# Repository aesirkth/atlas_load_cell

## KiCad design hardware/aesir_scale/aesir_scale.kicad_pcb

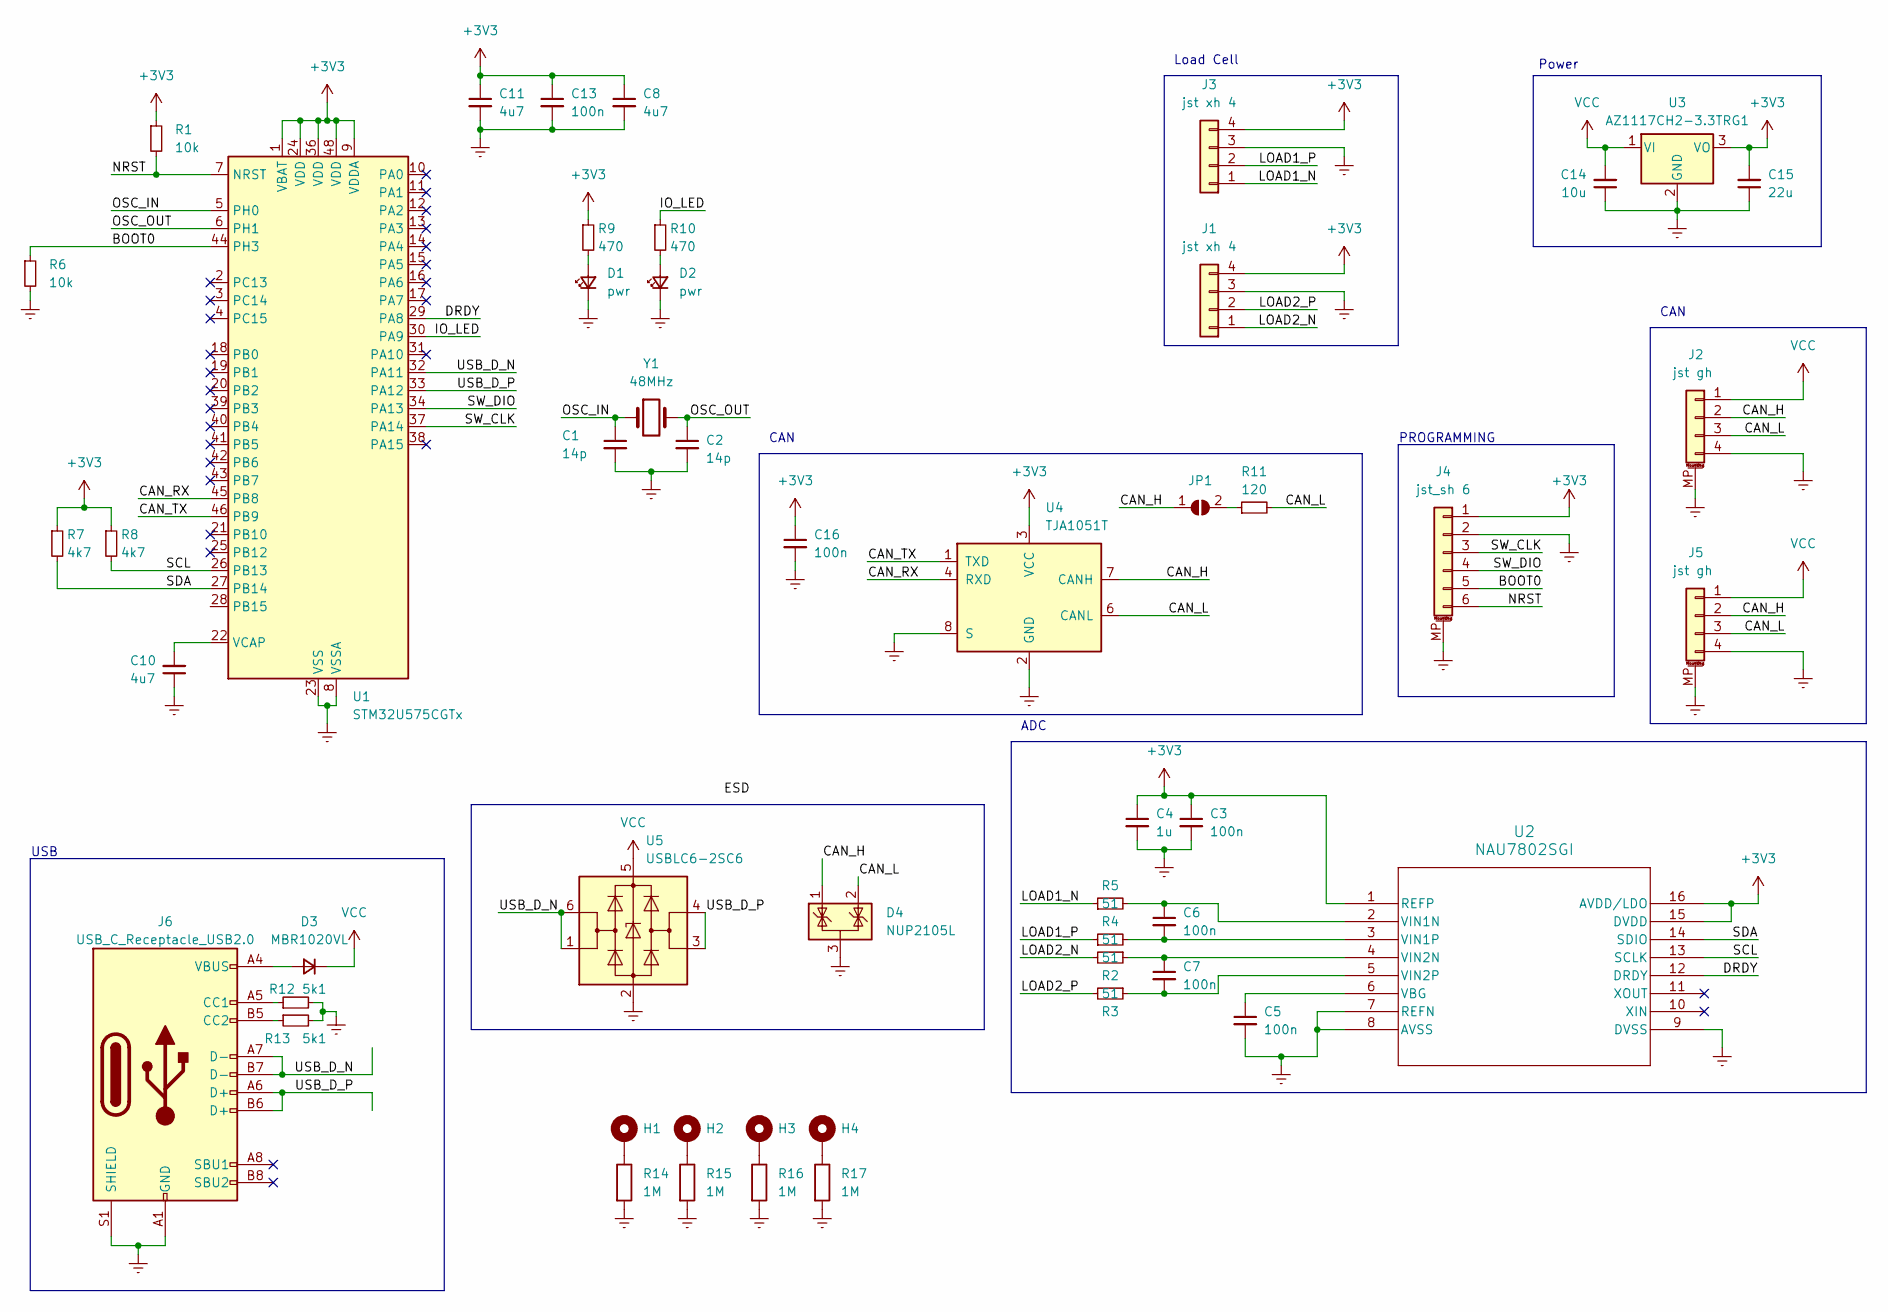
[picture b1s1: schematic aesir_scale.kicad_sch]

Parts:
C1, C2: 14p; C_0603_1608Metric_Pad1.08x0.95mm_HandSolder
C3, C5, C6, C7, C13, C16: 100n; C_0603_1608Metric_Pad1.08x0.95mm_HandSolder
C4: 1u; C_0603_1608Metric_Pad1.08x0.95mm_HandSolder
C8, C10, C11: 4u7; C_0603_1608Metric_Pad1.08x0.95mm_HandSolder
C14: 10u; C_0603_1608Metric_Pad1.08x0.95mm_HandSolder
C15: 22u; C_0603_1608Metric_Pad1.08x0.95mm_HandSolder
D1, D2: pwr; LED_0805_2012Metric_Pad1.15x1.40mm_HandSolder
D3: MBR1020VL; D_SOD-323_HandSoldering
D4: NUP2105L; SOT-23
H1, H2, H3, H4: MountingHole; MountingHole_3.2mm_M3_ISO7380_Pad
J1, J3: jst xh 4; JST_XH_B4B-XH-A_1x04_P2.50mm_Vertical
J2, J5: jst gh; JST_GH_SM04B-GHS-TB_1x04-1MP_P1.25mm_Horizontal
J4: jst_sh 6; JST_SH_SM06B-SRSS-TB_1x06-1MP_P1.00mm_Horizontal
J6: USB_C_Receptacle_USB2.0; USB_C_Receptacle_Palconn_UTC16-G
JP1: SolderJumper_2_Open; SolderJumper-2_P1.3mm_Open_TrianglePad1.0x1.5mm
R1, R6: 10k; R_0603_1608Metric_Pad0.98x0.95mm_HandSolder
R2, R3, R4, R5: 51; R_0603_1608Metric_Pad0.98x0.95mm_HandSolder
R7, R8: 4k7; R_0603_1608Metric_Pad0.98x0.95mm_HandSolder
R9, R10: 470; R_0603_1608Metric_Pad0.98x0.95mm_HandSolder
R11: 120; R_0603_1608Metric_Pad0.98x0.95mm_HandSolder
R12, R13: 5k1; R_0603_1608Metric
R14, R15, R16, R17: 1M; R_0603_1608Metric_Pad0.98x0.95mm_HandSolder
U1: STM32U575CGTx; LQFP-48_7x7mm_P0.5mm
U2: NAU7802SGI; SOI16_NAU7802SGI_NUV
U3: AZ1117CH2-3.3TRG1; SOT-223-3_TabPin2
U4: TJA1051T; SOIC-8_3.9x4.9mm_P1.27mm
U5: USBLC6-2SC6; SOT-23-6
Y1: 48MHz; Crystal_SMD_0603-2Pin_6.0x3.5mm_HandSoldering

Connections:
+3V3: C3.1, C4.1, C8.1, C11.1, C13.1, C15.2, C16.1, J1.4, J3.4, J4.1, R1.1, R7.1, R8.1, R9.1, U1.1 (VBAT), U1.9 (VDDA), U1.24 (VDD), U1.36 (VDD), U1.48 (VDD), U2.1 (REFP), U2.15 (DVDD), U2.16 (AVDD/LDO), U3.3 (VO), U4.3 (VCC)
/BOOT0: J4.5, R6.1, U1.44 (PH3)
/CAN_H: D4.1 (K), J2.2, J5.2, JP1.1 (A), U4.7 (CANH)
/CAN_L: D4.2 (K), J2.3, J5.3, R11.2, U4.6 (CANL)
/CAN_RX: U1.45 (PB8), U4.4 (RXD)
/CAN_TX: U1.46 (PB9), U4.1 (TXD)
/DRDY: U1.29 (PA8), U2.12 (DRDY)
/IO_LED: R10.1, U1.30 (PA9)
/LOAD1_N: J3.1, R5.1
/LOAD1_P: J3.2, R4.1
/LOAD2_N: J1.1, R2.2
/LOAD2_P: J1.2, R3.2
/NRST: J4.6, R1.2, U1.7 (NRST)
/OSC_IN: C1.1, U1.5 (PH0), Y1.1
/OSC_OUT: C2.1, U1.6 (PH1), Y1.2
/SCL: R8.2, U1.26 (PB13), U2.13 (SCLK)
/SDA: R7.2, U1.27 (PB14), U2.14 (SDIO)
/SW_CLK: J4.3, U1.37 (PA14)
/SW_DIO: J4.4, U1.34 (PA13)
/USB_D_N: J6.A7 (D-), J6.B7 (D-), U1.32 (PA11), U5.1 (I/O1), U5.6 (I/O1)
/USB_D_P: J6.A6 (D+), J6.B6 (D+), U1.33 (PA12), U5.3 (I/O2), U5.4 (I/O2)
Earth: C1.2, C2.2, C3.2, C4.2, C5.2, C8.2, C10.1, C11.2, C13.2, C14.1, C15.1, C16.2, D1.1 (K), D2.1 (K), D4.3 (A), J1.3, J2.4, J2.MP (MountPin), J3.3, J4.2, J4.MP (MountPin), J5.4, J5.MP (MountPin), J6.A1 (GND), J6.A12 (GND), J6.B1 (GND), J6.B12 (GND), J6.S1 (SHIELD), R6.2, R12.2, R13.2, R14.2, R15.2, R16.2, R17.2, U1.8 (VSSA), U1.23 (VSS), U1.35 (VSS), U1.47 (VSS), U2.7 (REFN), U2.8 (AVSS), U2.9 (DVSS), U3.2 (GND), U4.2 (GND), U4.8 (S), U5.2 (GND)
unnamed: D1.2 (A), R9.2
unnamed: D2.2 (A), R10.2
unnamed: D3.2 (A), J6.A4 (VBUS), J6.A9 (VBUS), J6.B4 (VBUS), J6.B9 (VBUS)
unnamed: H1.1, R14.1
unnamed: H2.1, R15.1
unnamed: H3.1, R16.1
unnamed: H4.1, R17.1
unnamed: J6.A5 (CC1), R12.1
unnamed: J6.B5 (CC2), R13.1
unnamed: JP1.2 (B), R11.1
unnamed: C10.2, U1.22 (VCAP)
unnamed: C5.1, U2.6 (VBG)
unnamed: C6.1, R5.2, U2.2 (VIN1N)
unnamed: C6.2, R4.2, U2.3 (VIN1P)
unnamed: C7.1, R2.1, U2.4 (VIN2N)
unnamed: C7.2, R3.1, U2.5 (VIN2P)
VCC: C14.2, D3.1 (K), J2.1, J5.1, U3.1 (VI), U5.5 (VBUS)

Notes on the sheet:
Power
CAN
USB
PROGRAMMING
ADC
Load Cell

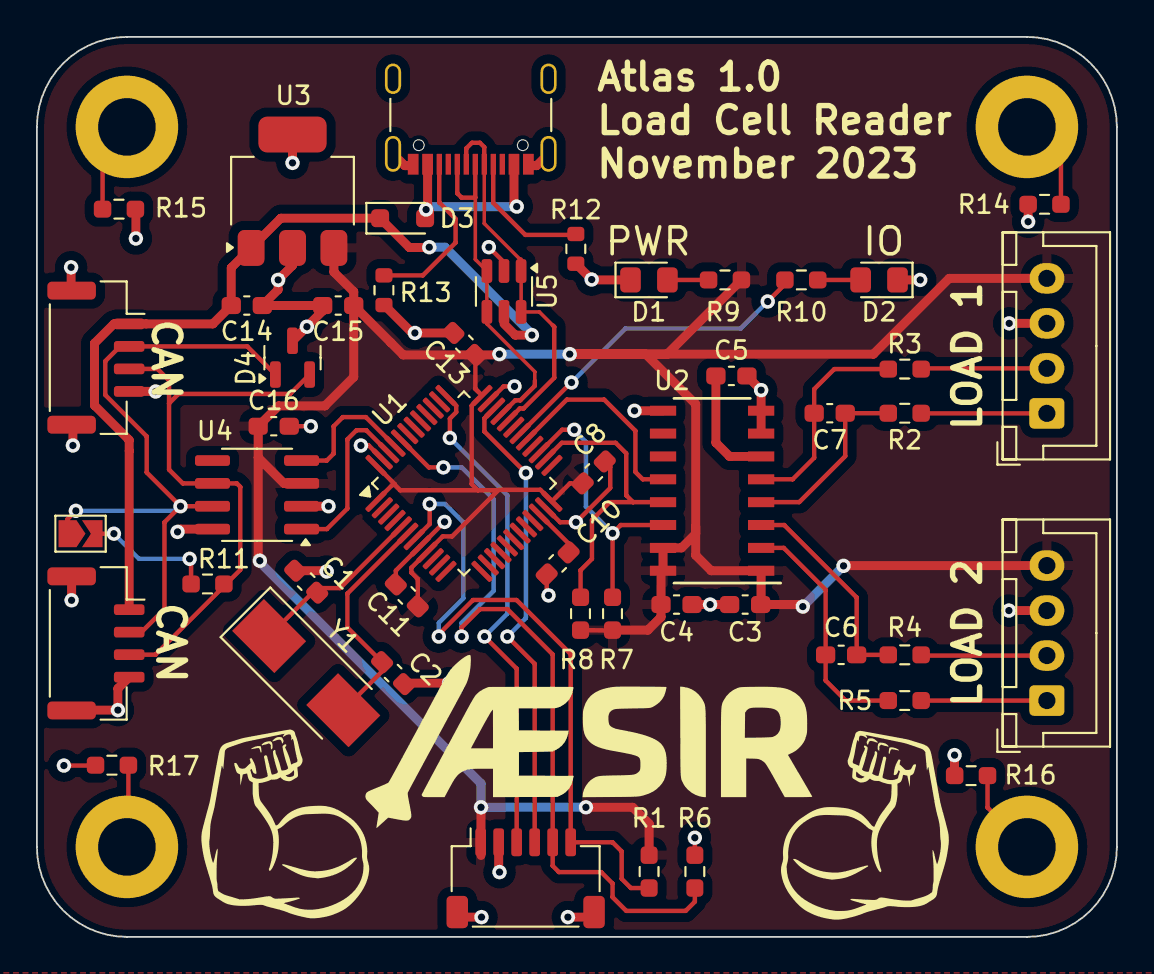
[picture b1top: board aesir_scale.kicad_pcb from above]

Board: 2 copper layers, 60.0 x 50.0 mm, 52 parts (0 on the bottom side), 39 nets.

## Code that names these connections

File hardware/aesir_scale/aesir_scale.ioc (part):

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Mcu.Name=STM32U575CGTx
Mcu.Package=LQFP48
Mcu.UserName=STM32U575CGTx
PB13.Signal=I2C2_SCL
PB14.Signal=I2C2_SDA
PB8.Mode=FDCAN_Activate
PB8.Signal=FDCAN1_RX
PB9.Mode=FDCAN_Activate
PB9.Signal=FDCAN1_TX
RCC.HSE_VALUE=16000000
board=custom

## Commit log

2023-11-17 USB diode & CAN jumper
2023-11-20 add caps
2023-11-28 add pdf
2025-03-17 correct i2c bus
2025-03-23 update gitignore
2025-03-28 set up env and blinky
2025-03-28 add swd to Makefile
2025-04-04 cleanup and correct led name
2025-04-11 usb cdc working
2025-04-11 west.yml
2025-04-11 readme install instructions
2025-09-03 Updated Version
2025-09-03 build: make Zephyr lookup explicit in CMakeLists
2025-10-09 fix env
2025-10-09 readme: add cloning instructions
2025-10-09 west.yml ref main
2025-10-09 do not override pip packages
2025-10-09 update Makefile
2025-10-09 temporarily remove NAU from dts
2025-10-09 Makefile: add clean
2025-10-09 add udev rules
2025-10-09 readme: fix flash instructions
2025-10-09 westl.yml: fix
2025-10-31 integrated NAU7802 driver module in build
